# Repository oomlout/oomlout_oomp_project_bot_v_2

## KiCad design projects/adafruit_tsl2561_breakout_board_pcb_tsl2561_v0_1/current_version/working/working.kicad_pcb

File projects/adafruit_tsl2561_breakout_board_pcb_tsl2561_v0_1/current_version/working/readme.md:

# tsl2561_breakout_board_pcb
 
## summary 
* id: adafruit_tsl2561_breakout_board_pcb_tsl2561_v0_1
* user: adafruit
* name: tsl2561_breakout_board_pcb
* board: tsl2561_v0_1
* repo: https://github.com/adafruit/TSL2561-breakout-board-PCB

* src_file_repo_sch: 
* src_file_repo_sch_link: https://github.com/adafruit/TSL2561-breakout-board-PCB/tree/master/
* full details link: https://github.com/oomlout/oomlout_oomp_project_bot_v_2/tree/main/projects/adafruit_tsl2561_breakout_board_pcb_tsl2561_v0_1/current_version/working  

## schematic  
  
[schematic (pdf)](working_schematic.pdf) 

## pcb  

[board (pdf)](working.pdf)  

## working_bom
| Id | Designator | Footprint | Quantity | Designation | Supplier and ref |  | None | 
| --- | --- | --- | --- | --- | --- | --- | --- | 
| 1 | @HOLE1,@HOLE0 |  | 2 |  |  |  | [''] | 
| 2 | FID1,FID2 | FIDUCIAL_1MM | 2 | FIDUCIAL_1MM |  |  | [''] | 
| 3 | VIN_PAD0,SDA_PAD0,SCL_PAD0,GND_PAD0 | SEWALLI | 4 | SEWTAP-ALLIGATOR |  |  | [''] | 
| 4 | U$4 | STEMMA_TSL2561_B_FRONT | 1 |  |  |  | [''] | 
| 5 | X1 | JSTPH4 | 1 | STEMMA_I2C_RASMT |  |  | [''] | 
| 6 | C2,C1 | 0805-NO | 2 | 10uF |  |  | [''] | 
| 7 | R1 | RESPACK_4X0603 | 1 | 10K |  |  | [''] | 
| 8 | U2 | SOT23-5 | 1 | MIC5225-3.3 |  |  | [''] | 
| 9 | Q3 | SOT363 | 1 | 2N7002D |  |  | [''] | 
| 10 | U3 | TSL2561_FN | 1 | TSL2561 |  |  | [''] | 
| 11 | U$8 | PCBFEAT-REV-040 | 1 |  |  |  | [''] | 
| 12 | U$7 | STEMMA_TSL2561_B_BACK | 1 |  |  |  | [''] | 
| 13 | SJ1 | SOLDERJUMPER_2WAY_OPEN_NOPASTE | 1 |  |  |  | [''] | 

## bom_schematic
| Ref | Qnty | Value | Cmp name | Footprint | Description | Vendor | DNP | 
| --- | --- | --- | --- | --- | --- | --- | --- | 
| C1, C2 | 2 | 10uF | CAP_CERAMIC0805-NOOUTLINE | working:0805-NO |  |  |  | 
| FID1, FID2 | 2 | FIDUCIAL_1MM | FIDUCIAL_1MM | working:FIDUCIAL_1MM |  |  |  | 
| GND_PAD0 | 1 | SEWTAP-ALLIGATOR | SEWTAP-ALLIGATOR | working:SEWALLI |  |  |  | 
| Q3 | 1 | 2N7002D | MOSFET-N_DUAL | working:SOT363 |  |  |  | 
| R1 | 1 | 10K | RESISTOR_4PACK | working:RESPACK_4X0603 |  |  |  | 
| SCL_PAD0 | 1 | SEWTAP-ALLIGATOR | SEWTAP-ALLIGATOR | working:SEWALLI |  |  |  | 
| SDA_PAD0 | 1 | SEWTAP-ALLIGATOR | SEWTAP-ALLIGATOR | working:SEWALLI |  |  |  | 
| SJ1 | 1 | SOLDERJUMPER_2WAY | SOLDERJUMPER_2WAY | working:SOLDERJUMPER_2WAY_OPEN_NOPASTE |  |  |  | 
| U2 | 1 | MIC5225-3.3 | VREG_SOT23-5 | working:SOT23-5 |  |  |  | 
| U3 | 1 | TSL2561 | LIGHT_TSL2561 | working:TSL2561_FN |  |  |  | 
| VIN_PAD0 | 1 | SEWTAP-ALLIGATOR | SEWTAP-ALLIGATOR | working:SEWALLI |  |  |  | 
| X1 | 1 | STEMMA_I2C_RASMT | STEMMA_I2C_RASMT | working:JSTPH4 |  |  |  |

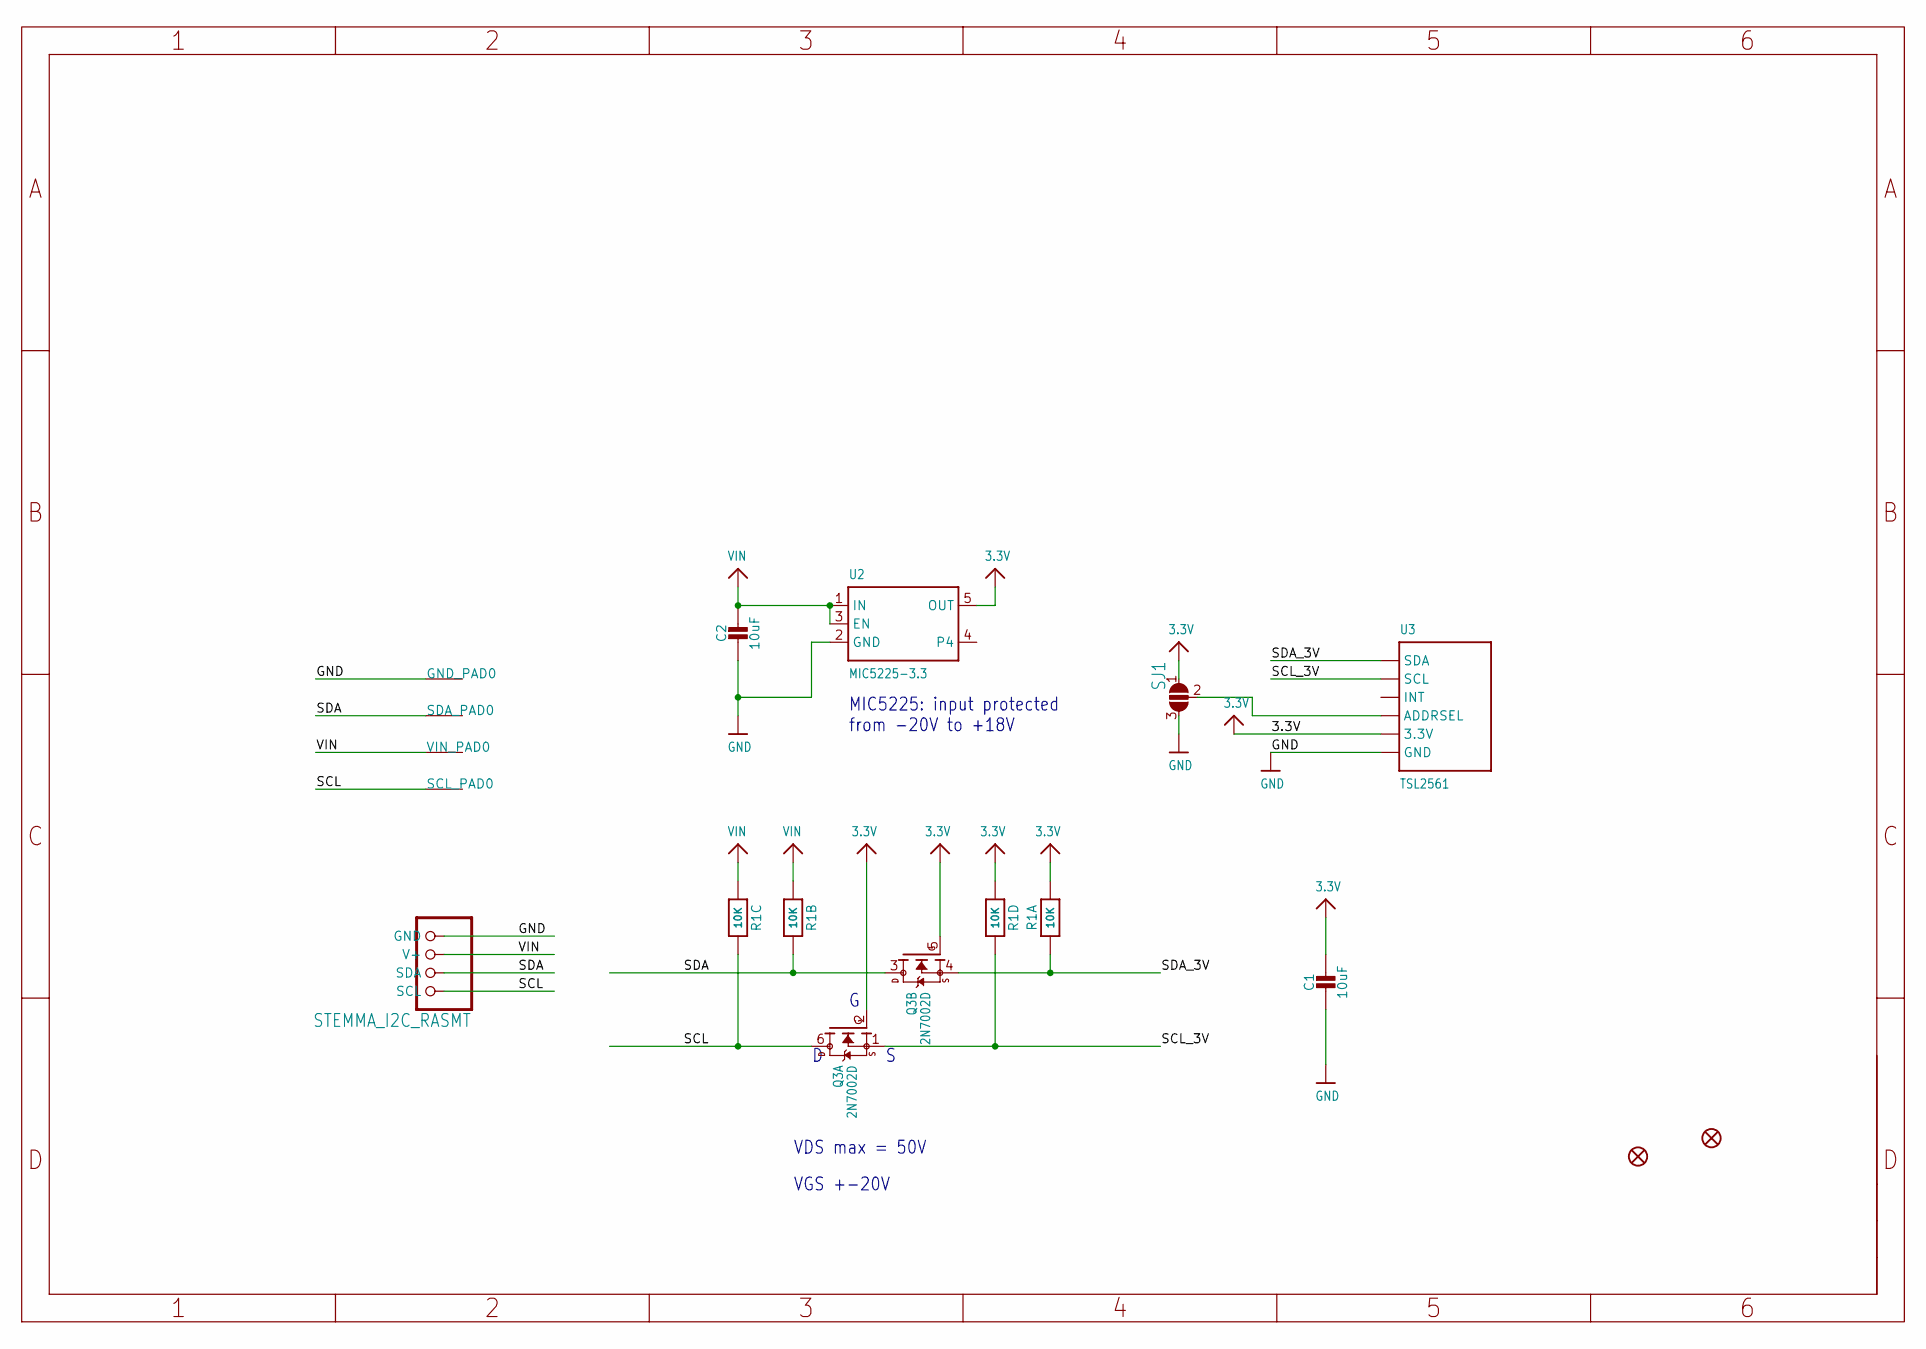
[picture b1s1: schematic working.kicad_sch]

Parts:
C1, C2: 10uF; 0805-NO
FID1, FID2: FIDUCIAL_1MM
GND_PAD0: SEWTAP-ALLIGATOR; SEWALLI
Q3: 2N7002D; SOT363
R1: 10K; RESPACK_4X0603
SCL_PAD0: SEWTAP-ALLIGATOR; SEWALLI
SDA_PAD0: SEWTAP-ALLIGATOR; SEWALLI
SJ1: SOLDERJUMPER_2WAY; SOLDERJUMPER_2WAY_OPEN_NOPASTE
U2: MIC5225-3.3; SOT23-5
U3: TSL2561; TSL2561_FN
VIN_PAD0: SEWTAP-ALLIGATOR; SEWALLI
X1: STEMMA_I2C_RASMT; JSTPH4

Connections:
3.3V: C1.1, Q3.2 (G), Q3.5 (G), R1.1, R1.5 (2), SJ1.1, U2.5 (OUT), U3.VDD (3.3V)
GND: C1.2, C2.2, GND_PAD0.P$1, SJ1.3, U2.2 (GND), U3.VSS (GND), X1.1 (GND)
unnamed: SJ1.2, U3.ADR (ADDRSEL)
SCL: Q3.6 (D), R1.6 (2), SCL_PAD0.P$1, X1.4 (SCL)
SCL_3V: Q3.1 (S), R1.4 (1), U3.CLK (SCL)
SDA: Q3.3 (D), R1.7 (2), SDA_PAD0.P$1, X1.3 (SDA)
SDA_3V: Q3.4 (S), R1.8 (2), U3.DATA (SDA)
VIN: C2.1, R1.2 (1), R1.3 (1), U2.1 (IN), U2.3 (EN), VIN_PAD0.P$1, X1.2 (V+)

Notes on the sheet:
VGS +-20V
MIC5225: input protected from -20V to +18V
VDS max = 50V

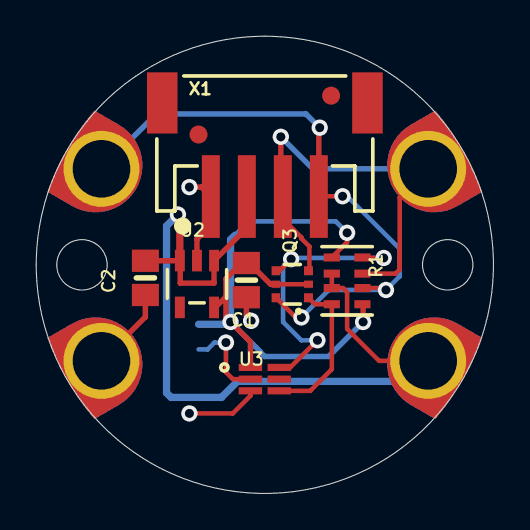
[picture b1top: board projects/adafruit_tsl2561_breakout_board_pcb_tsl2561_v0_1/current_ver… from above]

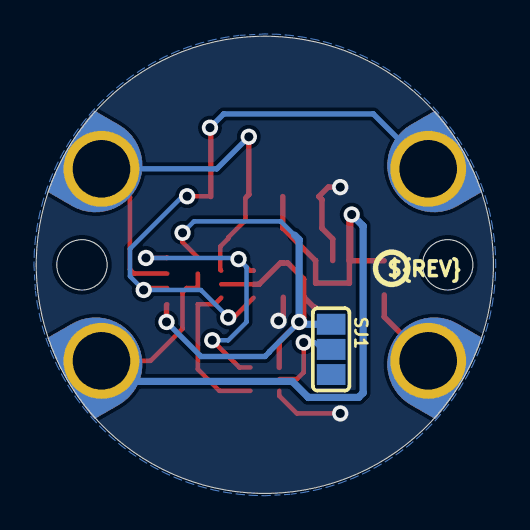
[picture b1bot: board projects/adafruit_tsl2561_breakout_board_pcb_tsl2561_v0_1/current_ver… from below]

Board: 2 copper layers, 25.4 x 25.4 mm, 19 parts (3 on the bottom side), 8 nets.

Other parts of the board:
@HOLE0, @HOLE1: (no value)
U$4: STEMMA_TSL2561_B_FRONT
U$7: STEMMA_TSL2561_B_BACK
U$8: PCBFEAT-REV-040

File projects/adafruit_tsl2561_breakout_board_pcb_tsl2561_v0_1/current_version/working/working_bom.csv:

"Id";"Designator";"Footprint";"Quantity";"Designation";"Supplier and ref";
1;"@HOLE1,@HOLE0";"";2;"";;;
2;"FID1,FID2";"FIDUCIAL_1MM";2;"FIDUCIAL_1MM";;;
3;"VIN_PAD0,SDA_PAD0,SCL_PAD0,GND_PAD0";"SEWALLI";4;"SEWTAP-ALLIGATOR";;;
4;"U$4";"STEMMA_TSL2561_B_FRONT";1;"";;;
5;"X1";"JSTPH4";1;"STEMMA_I2C_RASMT";;;
6;"C2,C1";"0805-NO";2;"10uF";;;
7;"R1";"RESPACK_4X0603";1;"10K";;;
8;"U2";"SOT23-5";1;"MIC5225-3.3";;;
9;"Q3";"SOT363";1;"2N7002D";;;
10;"U3";"TSL2561_FN";1;"TSL2561";;;
11;"U$8";"PCBFEAT-REV-040";1;"";;;
12;"U$7";"STEMMA_TSL2561_B_BACK";1;"";;;
13;"SJ1";"SOLDERJUMPER_2WAY_OPEN_NOPASTE";1;"";;;

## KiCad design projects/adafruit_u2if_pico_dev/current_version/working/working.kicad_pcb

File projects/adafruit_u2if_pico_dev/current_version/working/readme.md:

# u2if
 
## summary 
* id: adafruit_u2if_pico_dev
* user: adafruit
* name: u2if
* board: pico_dev
* repo: https://github.com/adafruit/u2if
* src_file_repo_kicad_pcb: board/pico-dev-v2/pico-dev.kicad_pcb
* src_file_repo_kicad_pcb_link: https://github.com/adafruit/u2if/tree/main/board/pico-dev-v2/pico-dev.kicad_pcb

* src_file_repo_sch: board/pico-dev-v2/pico-dev.sch
* src_file_repo_sch_link: https://github.com/adafruit/u2if/tree/main/board/pico-dev-v2/pico-dev.sch
* full details link: https://github.com/oomlout/oomlout_oomp_project_bot_v_2/tree/main/projects/adafruit_u2if_pico_dev/current_version/working  

## schematic  
  
[schematic (pdf)](working_schematic.pdf) 

## pcb  

[board (pdf)](working.pdf)  

## working_bom
| Id | Designator | Footprint | Quantity | Designation | Supplier and ref |  | None | 
| --- | --- | --- | --- | --- | --- | --- | --- | 
| 1 | U1 | RPi_Pico_SMD_TH | 1 | Pico |  |  | [''] | 
| 2 | U2 | ssd1306_I2c | 1 | SSD1306_I2C |  |  | [''] | 
| 3 | J10,J9 | PinHeader_1x06_P2.54mm_Vertical | 2 | SPI0 |  |  | [''] | 
| 4 | J8 | PinHeader_1x03_P2.54mm_Vertical | 1 | UART0 |  |  | [''] | 
| 5 | J17,J13 | PinHeader_1x03_P2.54mm_Vertical | 2 | +3.3V |  |  | [''] | 
| 6 | SW2 | SW_PUSH_6mm_H4.3mm | 1 | SW_GP9 |  |  | [''] | 
| 7 | SW3 | SW_PUSH_6mm_H4.3mm | 1 | SW_GP8 |  |  | [''] | 
| 8 | J3 | PinHeader_1x04_P2.54mm_Vertical | 1 | ANALOG |  |  | [''] | 
| 9 | J16,J15 | PinHeader_1x03_P2.54mm_Vertical | 2 | GND |  |  | [''] | 
| 10 | J19 | PinHeader_1x05_P2.54mm_Vertical | 1 | I2S |  |  | [''] | 
| 11 | C3,C4,C2,C5 | CP_Radial_D6.3mm_P2.50mm | 4 | CP |  |  | [''] | 
| 12 | SW1 | SW_PUSH_6mm_H4.3mm | 1 | RESET |  |  | [''] | 
| 13 | D2 | LED_1206_3216Metric_Pad1.42x1.75mm_HandSolder | 1 | LED |  |  | [''] | 
| 14 | R4 | R_1206_3216Metric_Pad1.42x1.75mm_HandSolder | 1 | 470 |  |  | [''] | 
| 15 | R3,R5,R2,R1,R6 | R_1206_3216Metric_Pad1.42x1.75mm_HandSolder | 5 | 10k |  |  | [''] | 
| 16 | J2 | PinHeader_1x04_P2.54mm_Vertical | 1 | SWD |  |  | [''] | 
| 17 | J21 | PinHeader_1x04_P2.54mm_Vertical | 1 | RGB |  |  | [''] | 
| 18 | JP1 | PinHeader_1x02_P2.54mm_Vertical | 1 | LCD_POWER |  |  | [''] | 
| 19 | J6,J5,J7 | PinHeader_1x04_P2.54mm_Vertical | 3 | I2C0 |  |  | [''] | 
| 20 | J20 | PinHeader_1x03_P2.54mm_Vertical | 1 | GPIO |  |  | [''] | 
| 21 | J18 | PinHeader_1x05_P2.54mm_Vertical | 1 | GPIO |  |  | [''] | 
| 22 | C1 | CP_Radial_D8.0mm_P3.50mm | 1 | CP |  |  | [''] | 
| 23 | J1 | PinHeader_1x02_P2.54mm_Vertical | 1 | MODE |  |  | [''] | 
| 24 | D1 | D_SMA | 1 | SS14 |  |  | [''] | 
| 25 | J22,J23 | PinHeader_1x04_P2.54mm_Vertical | 2 | I2C1 |  |  | [''] | 
| 26 | J14 | PinHeader_1x03_P2.54mm_Vertical | 1 | +5V |  |  | [''] | 
| 27 | J12 | PinHeader_1x06_P2.54mm_Vertical | 1 | SPI1/GPIO |  |  | [''] | 
| 28 | Q1 | SOT-23_Handsoldering | 1 | BSS138 |  |  | [''] | 

## bom_schematic
| Ref | Qnty | Value | Cmp name | Footprint | Description | Vendor | DNP | 
| --- | --- | --- | --- | --- | --- | --- | --- | 
| C1 | 1 | CP | CP-Device | Capacitor_THT:CP_Radial_D8.0mm_P3.50mm |  |  |  | 
| C2, C3, C4, C5 | 4 | CP | CP-Device | Capacitor_THT:CP_Radial_D6.3mm_P2.50mm |  |  |  | 
| D1 | 1 | SS14 | D_Schottky | Diode_SMD:D_SMA | Schottky diode |  |  | 
| D2 | 1 | LED | LED | LED_SMD:LED_1206_3216Metric_Pad1.42x1.75mm_HandSolder | Light emitting diode |  |  | 
| H1, H2, H3, H4 | 4 | MountingHole | MountingHole | MountingHole:MountingHole_3.2mm_M3 | Mounting Hole without connection |  |  | 
| J1 | 1 | MODE | Conn_01x02_Male-Connector | Connector_PinHeader_2.54mm:PinHeader_1x02_P2.54mm_Vertical |  |  |  | 
| J2 | 1 | SWD | Conn_01x04_Male-Connector | Connector_PinHeader_2.54mm:PinHeader_1x04_P2.54mm_Vertical |  |  |  | 
| J3 | 1 | ANALOG | Conn_01x04_Male-Connector | Connector_PinHeader_2.54mm:PinHeader_1x04_P2.54mm_Vertical |  |  |  | 
| J5, J6, J7 | 3 | I2C0 | Conn_01x04_Male-Connector | Connector_PinHeader_2.54mm:PinHeader_1x04_P2.54mm_Vertical |  |  |  | 
| J8 | 1 | UART0 | Conn_01x03_Male-Connector | Connector_PinHeader_2.54mm:PinHeader_1x03_P2.54mm_Vertical |  |  |  | 
| J9, J10 | 2 | SPI0 | Conn_01x06_Female-Connector | Connector_PinHeader_2.54mm:PinHeader_1x06_P2.54mm_Vertical |  |  |  | 
| J12 | 1 | SPI1/GPIO | Conn_01x06_Female-Connector | Connector_PinHeader_2.54mm:PinHeader_1x06_P2.54mm_Vertical |  |  |  | 
| J13, J17 | 2 | +3.3V | Conn_01x03_Male-Connector | Connector_PinHeader_2.54mm:PinHeader_1x03_P2.54mm_Vertical |  |  |  | 
| J14 | 1 | +5V | Conn_01x03_Male-Connector | Connector_PinHeader_2.54mm:PinHeader_1x03_P2.54mm_Vertical |  |  |  | 
| J15, J16 | 2 | GND | Conn_01x03_Male-Connector | Connector_PinHeader_2.54mm:PinHeader_1x03_P2.54mm_Vertical |  |  |  | 
| J18 | 1 | GPIO | Conn_01x05_Male-Connector | Connector_PinHeader_2.54mm:PinHeader_1x05_P2.54mm_Vertical |  |  |  | 
| J19 | 1 | I2S | Conn_01x05_Male-Connector | Connector_PinHeader_2.54mm:PinHeader_1x05_P2.54mm_Vertical |  |  |  | 
| J20 | 1 | GPIO | Conn_01x03_Male-Connector | Connector_PinHeader_2.54mm:PinHeader_1x03_P2.54mm_Vertical |  |  |  | 
| J21 | 1 | RGB | Conn_01x04_Male-Connector | Connector_PinHeader_2.54mm:PinHeader_1x04_P2.54mm_Vertical |  |  |  | 
| J22, J23 | 2 | I2C1 | Conn_01x04_Male-Connector | Connector_PinHeader_2.54mm:PinHeader_1x04_P2.54mm_Vertical |  |  |  | 
| JP1 | 1 | LCD_POWER | Jumper-Device | Connector_PinHeader_2.54mm:PinHeader_1x02_P2.54mm_Vertical |  |  |  | 
| Q1 | 1 | BSS138 | BSS138 | Package_TO_SOT_SMD:SOT-23_Handsoldering | 50V Vds, 0.22A Id, N-Channel MOSFET, SOT-23 |  |  | 
| R1, R2, R3, R5, R6 | 5 | 10k | R | Resistor_SMD:R_1206_3216Metric_Pad1.42x1.75mm_HandSolder | Resistor |  |  | 
| R4 | 1 | 470 | R | Resistor_SMD:R_1206_3216Metric_Pad1.42x1.75mm_HandSolder | Resistor |  |  | 
| SW1 | 1 | RESET | SW_Push | Button_Switch_THT:SW_PUSH_6mm_H4.3mm | Push button switch, generic, two pins |  |  | 
| SW2 | 1 | SW_GP9 | SW_Push | Button_Switch_THT:SW_PUSH_6mm_H4.3mm | Push button switch, generic, two pins |  |  | 
| SW3 | 1 | SW_GP8 | SW_Push | Button_Switch_THT:SW_PUSH_6mm_H4.3mm | Push button switch, generic, two pins |  |  | 
| U1 | 1 | Pico | Pico | MCU_RaspberryPi_and_Boards:RPi_Pico_SMD_TH |  |  |  | 
| U2 | 1 | SSD1306_I2C | SSD1306_I2C | oled_ssd1306:ssd1306_I2c | LCD 16x2 Alphanumeric gray backlight, 3 or 5 V VDD |  |  |

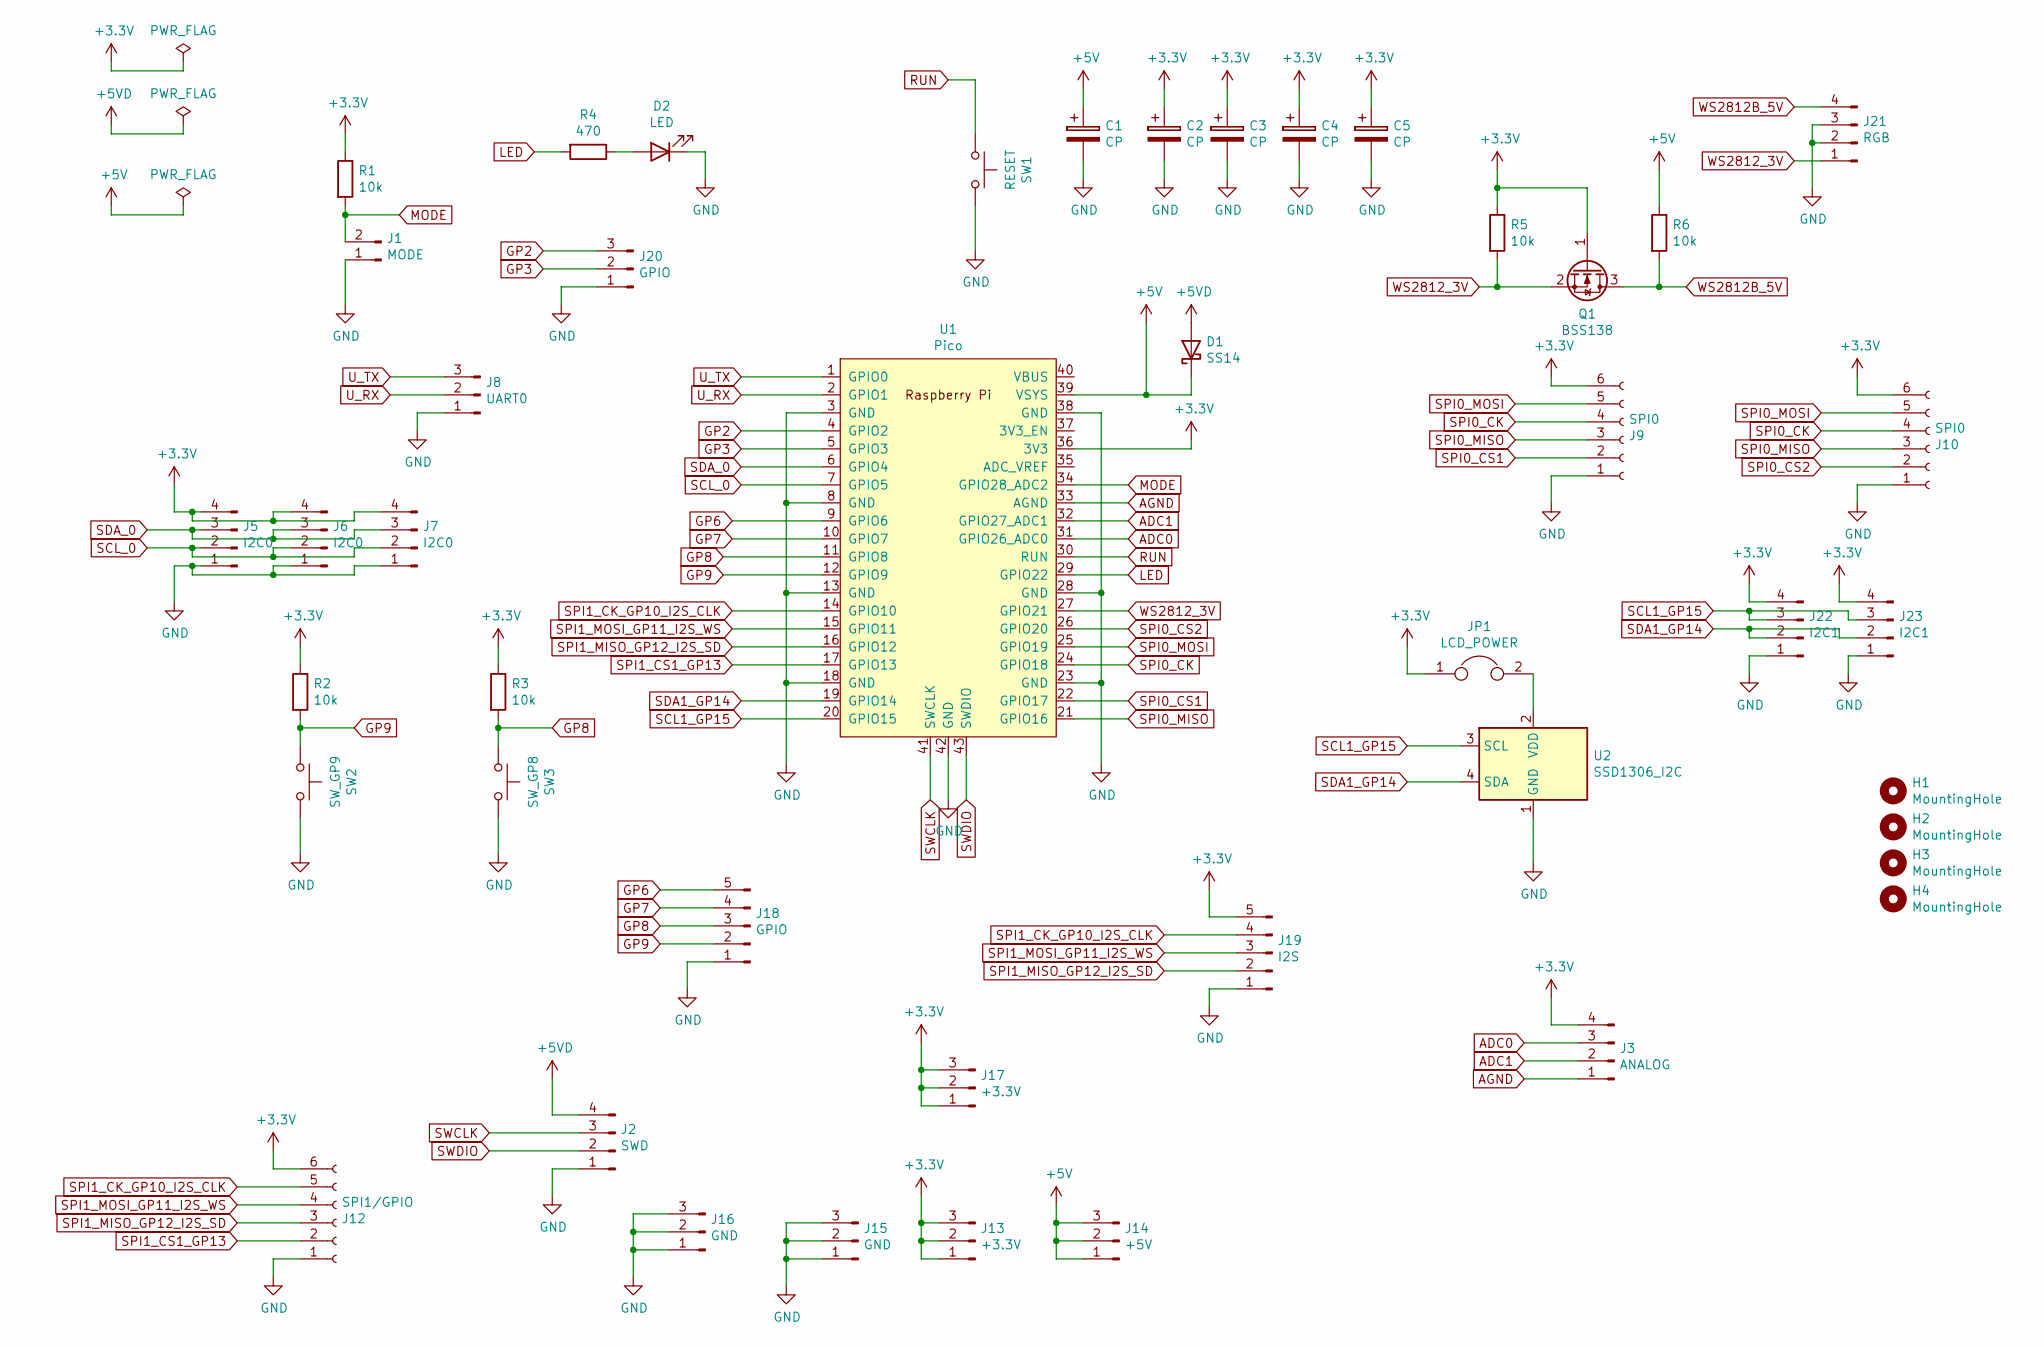
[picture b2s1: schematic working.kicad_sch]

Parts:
C1: CP; CP_Radial_D8.0mm_P3.50mm
C2, C3, C4, C5: CP; CP_Radial_D6.3mm_P2.50mm
D1: SS14; D_SMA
D2: LED; LED_1206_3216Metric_Pad1.42x1.75mm_HandSolder
H1, H2, H3, H4: MountingHole; MountingHole_3.2mm_M3
J1: MODE; PinHeader_1x02_P2.54mm_Vertical
J2: SWD; PinHeader_1x04_P2.54mm_Vertical
J3: ANALOG; PinHeader_1x04_P2.54mm_Vertical
J5, J6, J7: I2C0; PinHeader_1x04_P2.54mm_Vertical
J8: UART0; PinHeader_1x03_P2.54mm_Vertical
J9, J10: SPI0; PinHeader_1x06_P2.54mm_Vertical
J12: SPI1/GPIO; PinHeader_1x06_P2.54mm_Vertical
J13, J17: +3.3V; PinHeader_1x03_P2.54mm_Vertical
J14: +5V; PinHeader_1x03_P2.54mm_Vertical
J15, J16: GND; PinHeader_1x03_P2.54mm_Vertical
J18: GPIO; PinHeader_1x05_P2.54mm_Vertical
J19: I2S; PinHeader_1x05_P2.54mm_Vertical
J20: GPIO; PinHeader_1x03_P2.54mm_Vertical
J21: RGB; PinHeader_1x04_P2.54mm_Vertical
J22, J23: I2C1; PinHeader_1x04_P2.54mm_Vertical
JP1: LCD_POWER; PinHeader_1x02_P2.54mm_Vertical
Q1: BSS138; SOT-23_Handsoldering
R1, R2, R3, R5, R6: 10k; R_1206_3216Metric_Pad1.42x1.75mm_HandSolder
R4: 470; R_1206_3216Metric_Pad1.42x1.75mm_HandSolder
SW1: RESET; SW_PUSH_6mm_H4.3mm
SW2: SW_GP9; SW_PUSH_6mm_H4.3mm
SW3: SW_GP8; SW_PUSH_6mm_H4.3mm
U1: Pico; RPi_Pico_SMD_TH
U2: SSD1306_I2C; ssd1306_I2c

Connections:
+3V3: C2.1, C3.1, C4.1, C5.1, J3.4, J5.4, J6.4, J7.4, J9.6, J10.6, J12.6, J13.1, J13.2, J13.3, J17.1, J17.2, J17.3, J19.5, J22.4, J23.4, JP1.1, Q1.1 (G), R1.1, R2.1, R3.1, R5.1, U1.36 (3V3)
+5V: C1.1, D1.1 (K), J14.1, J14.2, J14.3, R6.1, U1.39 (VSYS)
+5VD: D1.2 (A), J2.4
ADC0: J3.3, U1.31 (GPIO26_ADC0)
ADC1: J3.2, U1.32 (GPIO27_ADC1)
AGND: J3.1, U1.33 (AGND)
GND: C1.2, C2.2, C3.2, C4.2, C5.2, D2.1 (K), J1.1, J2.1, J5.1, J6.1, J7.1, J8.1, J9.1, J10.1, J12.1, J15.1, J15.2, J15.3, J16.1, J16.2, J16.3, J18.1, J19.1, J20.1, J21.2, J21.3, J22.1, J23.1, SW1.2, SW2.2, SW3.2, U1.3 (GND), U1.8 (GND), U1.13 (GND), U1.18 (GND), U1.23 (GND), U1.28 (GND), U1.38 (GND), U1.42 (GND), U2.1 (GND)
GP2: J20.3, U1.4 (GPIO2)
GP3: J20.2, U1.5 (GPIO3)
GP6: J18.5, U1.9 (GPIO6)
GP7: J18.4, U1.10 (GPIO7)
GP8: J18.3, R3.2, SW3.1, U1.11 (GPIO8)
GP9: J18.2, R2.2, SW2.1, U1.12 (GPIO9)
LED: R4.2, U1.29 (GPIO22)
MODE: J1.2, R1.2, U1.34 (GPIO28_ADC2)
unnamed: D2.2 (A), R4.1
unnamed: JP1.2, U2.2 (VDD)
RUN: SW1.1, U1.30 (RUN)
SCL1_GP15: J22.3, J23.3, U1.20 (GPIO15), U2.3 (SCL)
SCL_0: J5.2, J6.2, J7.2, U1.7 (GPIO5)
SDA1_GP14: J22.2, J23.2, U1.19 (GPIO14), U2.4 (SDA)
SDA_0: J5.3, J6.3, J7.3, U1.6 (GPIO4)
SPI0_CK: J9.4, J10.4, U1.24 (GPIO18)
SPI0_CS1: J9.2, U1.22 (GPIO17)
SPI0_CS2: J10.2, U1.26 (GPIO20)
SPI0_MISO: J9.3, J10.3, U1.21 (GPIO16)
SPI0_MOSI: J9.5, J10.5, U1.25 (GPIO19)
SPI1_CK_GP10_I2S_CLK: J12.5, J19.4, U1.14 (GPIO10)
SPI1_CS1_GP13: J12.2, U1.17 (GPIO13)
SPI1_MISO_GP12_I2S_SD: J12.3, J19.2, U1.16 (GPIO12)
SPI1_MOSI_GP11_I2S_WS: J12.4, J19.3, U1.15 (GPIO11)
SWCLK: J2.3, U1.41 (SWCLK)
SWDIO: J2.2, U1.43 (SWDIO)
U_RX: J8.2, U1.2 (GPIO1)
U_TX: J8.3, U1.1 (GPIO0)
WS2812B_5V: J21.4, Q1.3 (D), R6.2
WS2812_3V: J21.1, Q1.2 (S), R5.2, U1.27 (GPIO21)

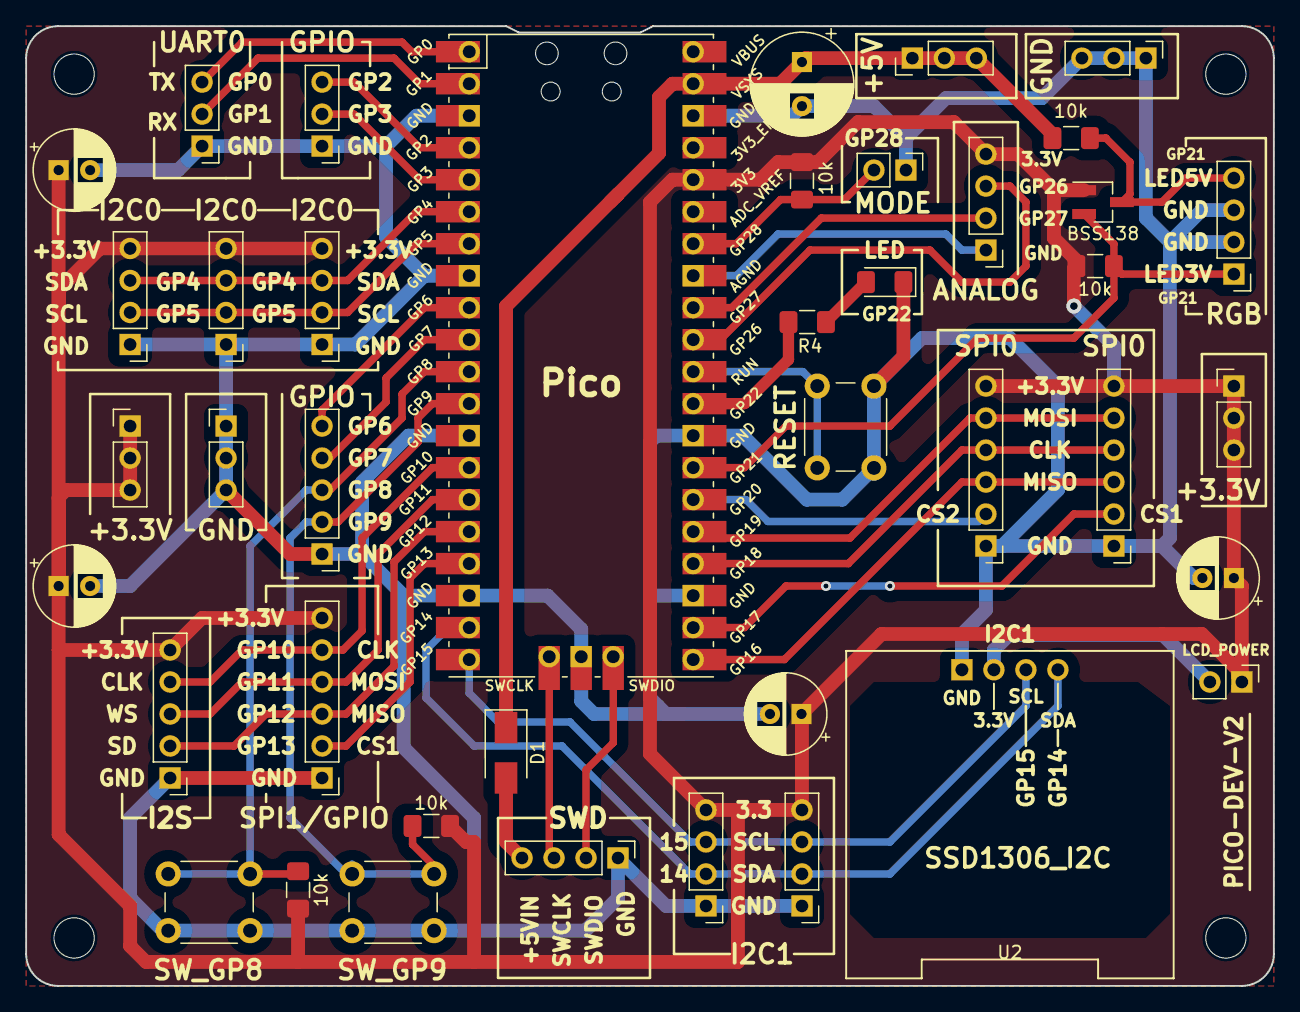
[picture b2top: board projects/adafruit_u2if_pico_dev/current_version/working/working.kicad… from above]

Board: 2 copper layers, 99.1 x 76.2 mm, 45 parts (0 on the bottom side), 37 nets.

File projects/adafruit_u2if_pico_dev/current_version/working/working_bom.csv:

"Id";"Designator";"Footprint";"Quantity";"Designation";"Supplier and ref";
1;"U1";"RPi_Pico_SMD_TH";1;"Pico";;;
2;"U2";"ssd1306_I2c";1;"SSD1306_I2C";;;
3;"J10,J9";"PinHeader_1x06_P2.54mm_Vertical";2;"SPI0";;;
4;"J8";"PinHeader_1x03_P2.54mm_Vertical";1;"UART0";;;
5;"J17,J13";"PinHeader_1x03_P2.54mm_Vertical";2;"+3.3V";;;
6;"SW2";"SW_PUSH_6mm_H4.3mm";1;"SW_GP9";;;
7;"SW3";"SW_PUSH_6mm_H4.3mm";1;"SW_GP8";;;
8;"J3";"PinHeader_1x04_P2.54mm_Vertical";1;"ANALOG";;;
9;"J16,J15";"PinHeader_1x03_P2.54mm_Vertical";2;"GND";;;
10;"J19";"PinHeader_1x05_P2.54mm_Vertical";1;"I2S";;;
11;"C3,C4,C2,C5";"CP_Radial_D6.3mm_P2.50mm";4;"CP";;;
12;"SW1";"SW_PUSH_6mm_H4.3mm";1;"RESET";;;
13;"D2";"LED_1206_3216Metric_Pad1.42x1.75mm_HandSolder";1;"LED";;;
14;"R4";"R_1206_3216Metric_Pad1.42x1.75mm_HandSolder";1;"470";;;
15;"R3,R5,R2,R1,R6";"R_1206_3216Metric_Pad1.42x1.75mm_HandSolder";5;"10k";;;
16;"J2";"PinHeader_1x04_P2.54mm_Vertical";1;"SWD";;;
17;"J21";"PinHeader_1x04_P2.54mm_Vertical";1;"RGB";;;
18;"JP1";"PinHeader_1x02_P2.54mm_Vertical";1;"LCD_POWER";;;
19;"J6,J5,J7";"PinHeader_1x04_P2.54mm_Vertical";3;"I2C0";;;
20;"J20";"PinHeader_1x03_P2.54mm_Vertical";1;"GPIO";;;
21;"J18";"PinHeader_1x05_P2.54mm_Vertical";1;"GPIO";;;
22;"C1";"CP_Radial_D8.0mm_P3.50mm";1;"CP";;;
23;"J1";"PinHeader_1x02_P2.54mm_Vertical";1;"MODE";;;
24;"D1";"D_SMA";1;"SS14";;;
25;"J22,J23";"PinHeader_1x04_P2.54mm_Vertical";2;"I2C1";;;
26;"J14";"PinHeader_1x03_P2.54mm_Vertical";1;"+5V";;;
27;"J12";"PinHeader_1x06_P2.54mm_Vertical";1;"SPI1/GPIO";;;
28;"Q1";"SOT-23_Handsoldering";1;"BSS138";;;

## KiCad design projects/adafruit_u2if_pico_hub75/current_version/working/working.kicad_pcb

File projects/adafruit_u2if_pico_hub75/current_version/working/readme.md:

# u2if
 
## summary 
* id: adafruit_u2if_pico_hub75
* user: adafruit
* name: u2if
* board: pico_hub75
* repo: https://github.com/adafruit/u2if
* src_file_repo_kicad_pcb: board/pico-hub75/pico-hub75.kicad_pcb
* src_file_repo_kicad_pcb_link: https://github.com/adafruit/u2if/tree/main/board/pico-hub75/pico-hub75.kicad_pcb

* src_file_repo_sch: board/pico-hub75/pico-hub75.sch
* src_file_repo_sch_link: https://github.com/adafruit/u2if/tree/main/board/pico-hub75/pico-hub75.sch
* full details link: https://github.com/oomlout/oomlout_oomp_project_bot_v_2/tree/main/projects/adafruit_u2if_pico_hub75/current_version/working  

## schematic  
  
[schematic (pdf)](working_schematic.pdf) 

## pcb  

[board (pdf)](working.pdf)  

## working_bom
| Id | Designator | Footprint | Quantity | Designation | Supplier and ref |  | None | 
| --- | --- | --- | --- | --- | --- | --- | --- | 
| 1 | U1 | RPi_Pico_SMD_TH | 1 | Pico |  |  | [''] | 
| 2 | J6,J7,J8 | PinHeader_1x03_P2.54mm_Vertical | 3 | Conn_01x03_Male |  |  | [''] | 
| 3 | SW3,SW1,SW2 | SW_PUSH_6mm_H5mm | 3 | SW_Push |  |  | [''] | 
| 4 | J5,J2 | PinHeader_1x06_P2.54mm_Vertical | 2 | Conn_01x06_Male |  |  | [''] | 
| 5 | J10,J9 | PinHeader_1x04_P2.54mm_Vertical | 2 | Conn_01x04_Male |  |  | [''] | 
| 6 | D1 | D_SMA | 1 | D_Schottky |  |  | [''] | 
| 7 | C5,C6,C8,C7 | CP_Radial_D6.3mm_P2.50mm | 4 | CP |  |  | [''] | 
| 8 | JP1,JP2 | PinHeader_1x02_P2.54mm_Vertical | 2 | Jumper |  |  | [''] | 
| 9 | J3 | PinHeader_1x05_P2.54mm_Vertical | 1 | Conn_01x05_Male |  |  | [''] | 
| 10 | J1 | IDC-Header_2x08_P2.54mm_Vertical | 1 | Conn_02x08_Odd_Even |  |  | [''] | 
| 11 | D2 | LED_1206_3216Metric_Pad1.42x1.75mm_HandSolder | 1 | LED |  |  | [''] | 
| 12 | R1,R2 | R_1206_3216Metric_Pad1.42x1.75mm_HandSolder | 2 | 10k |  |  | [''] | 
| 13 | R3 | R_1206_3216Metric_Pad1.42x1.75mm_HandSolder | 1 | 470 |  |  | [''] | 
| 14 | J4 | PinHeader_1x04_P2.54mm_Vertical | 1 | Conn_01x05_Male |  |  | [''] | 
| 15 | +5V,+3V3,GND | PinHeader_1x02_P2.54mm_Vertical | 3 | Conn_01x02_Male |  |  | [''] | 

## bom_schematic
| Ref | Qnty | Value | Cmp name | Footprint | Description | Vendor | DNP | 
| --- | --- | --- | --- | --- | --- | --- | --- | 
| C5, C6, C7, C8 | 4 | CP | CP-Device | Capacitor_THT:CP_Radial_D6.3mm_P2.50mm |  |  |  | 
| D1 | 1 | D_Schottky | D_Schottky | Diode_SMD:D_SMA | Schottky diode |  |  | 
| D2 | 1 | LED | LED | LED_SMD:LED_1206_3216Metric_Pad1.42x1.75mm_HandSolder | Light emitting diode |  |  | 
| H1, H2, H3, H4 | 4 | MountingHole | MountingHole | MountingHole:MountingHole_3.2mm_M3 | Mounting Hole without connection |  |  | 
| J1 | 1 | Conn_02x08_Odd_Even | Conn_02x08_Odd_Even | Connector_IDC:IDC-Header_2x08_P2.54mm_Vertical | Generic connector, double row, 02x08, odd/even pin numbering scheme (row 1 odd numbers, row 2 even numbers), script generated (kicad-library-utils/schlib/autogen/connector/) |  |  | 
| J2, J5 | 2 | Conn_01x06_Male | Conn_01x06_Male-Connector | Connector_PinHeader_2.54mm:PinHeader_1x06_P2.54mm_Vertical |  |  |  | 
| J3 | 1 | Conn_01x05_Male | Conn_01x05_Male-Connector | Connector_PinHeader_2.54mm:PinHeader_1x05_P2.54mm_Vertical |  |  |  | 
| J4 | 1 | Conn_01x05_Male | Conn_01x04_Male-Connector | Connector_PinHeader_2.54mm:PinHeader_1x04_P2.54mm_Vertical |  |  |  | 
| J6, J7, J8 | 3 | Conn_01x03_Male | Conn_01x03_Male-Connector | Connector_PinHeader_2.54mm:PinHeader_1x03_P2.54mm_Vertical |  |  |  | 
| J9, J10 | 2 | Conn_01x04_Male | Conn_01x04_Male-Connector | Connector_PinHeader_2.54mm:PinHeader_1x04_P2.54mm_Vertical |  |  |  | 
| J11, J12, J13 | 3 | Conn_01x02_Male | Conn_01x02_Male-Connector | Connector_PinHeader_2.54mm:PinHeader_1x02_P2.54mm_Vertical |  |  |  | 
| JP1, JP2 | 2 | Jumper | Jumper-Device | Connector_PinHeader_2.54mm:PinHeader_1x02_P2.54mm_Vertical |  |  |  | 
| R1, R2 | 2 | 10k | R | Resistor_SMD:R_1206_3216Metric_Pad1.42x1.75mm_HandSolder | Resistor |  |  | 
| R3 | 1 | 470 | R | Resistor_SMD:R_1206_3216Metric_Pad1.42x1.75mm_HandSolder | Resistor |  |  | 
| SW1, SW2, SW3 | 3 | SW_Push | SW_Push | Button_Switch_THT:SW_PUSH_6mm_H5mm | Push button switch, generic, two pins |  |  | 
| U1 | 1 | Pico | Pico | MCU_RaspberryPi_and_Boards:RPi_Pico_SMD_TH |  |  |  |

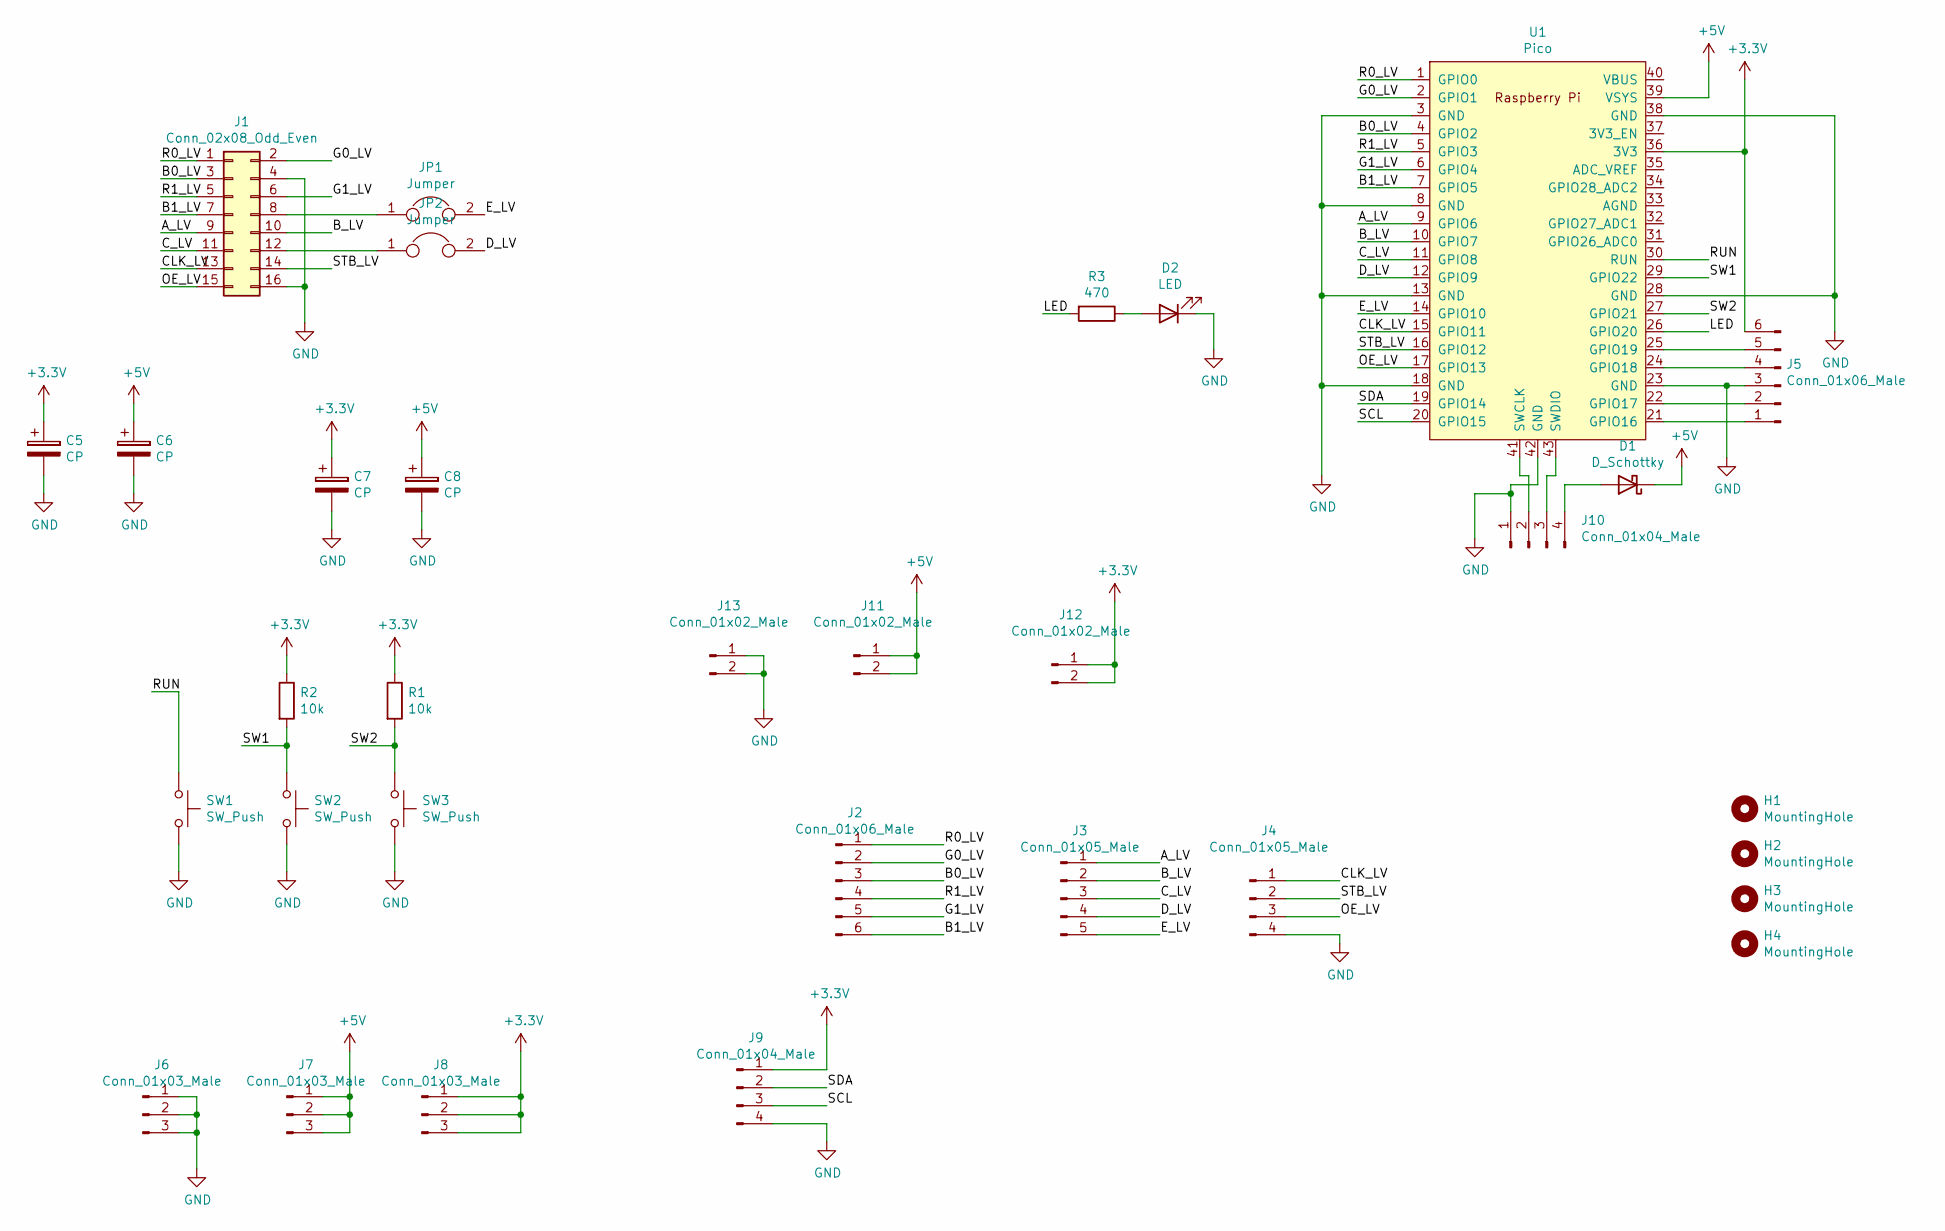
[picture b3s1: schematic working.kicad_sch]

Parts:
C5, C6, C7, C8: CP; CP_Radial_D6.3mm_P2.50mm
D1: D_Schottky; D_SMA
D2: LED; LED_1206_3216Metric_Pad1.42x1.75mm_HandSolder; LCSC C2296
H1, H2, H3, H4: MountingHole; MountingHole_3.2mm_M3
J1: Conn_02x08_Odd_Even; IDC-Header_2x08_P2.54mm_Vertical
J2, J5: Conn_01x06_Male; PinHeader_1x06_P2.54mm_Vertical
J3: Conn_01x05_Male; PinHeader_1x05_P2.54mm_Vertical
J4: Conn_01x05_Male; PinHeader_1x04_P2.54mm_Vertical
J6, J7, J8: Conn_01x03_Male; PinHeader_1x03_P2.54mm_Vertical
J9, J10: Conn_01x04_Male; PinHeader_1x04_P2.54mm_Vertical
J11, J12, J13: Conn_01x02_Male; PinHeader_1x02_P2.54mm_Vertical
JP1, JP2: Jumper; PinHeader_1x02_P2.54mm_Vertical
R1, R2: 10k; R_1206_3216Metric_Pad1.42x1.75mm_HandSolder; LCSC C17414
R3: 470; R_1206_3216Metric_Pad1.42x1.75mm_HandSolder; LCSC C17710
SW1, SW2, SW3: SW_Push; SW_PUSH_6mm_H5mm
U1: Pico; RPi_Pico_SMD_TH

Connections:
+3V3: C5.1, C7.1, J5.6, J8.1, J8.2, J8.3, J9.1, J12.1, J12.2, R1.1, R2.1, U1.36 (3V3); also elsewhere on the board
+5V: C6.1, C8.1, D1.1 (K), J7.1, J7.2, J7.3, J11.1, J11.2, U1.39 (VSYS); also elsewhere on the board
/A_LV: J1.9, J3.1, U1.9 (GPIO6)
/B0_LV: J1.3, J2.3, U1.4 (GPIO2)
/B1_LV: J1.7, J2.6, U1.7 (GPIO5)
/B_LV: J1.10, J3.2, U1.10 (GPIO7)
/CLK_LV: J1.13, J4.1, U1.15 (GPIO11)
/C_LV: J1.11, J3.3, U1.11 (GPIO8)
/D_LV: J3.4, JP2.2, U1.12 (GPIO9)
/E_LV: J3.5, JP1.2, U1.14 (GPIO10)
/G0_LV: J1.2, J2.2, U1.2 (GPIO1)
/G1_LV: J1.6, J2.5, U1.6 (GPIO4)
/LED: R3.2, U1.26 (GPIO20)
/OE_LV: J1.15, J4.3, U1.17 (GPIO13)
/R0_LV: J1.1, J2.1, U1.1 (GPIO0)
/R1_LV: J1.5, J2.4, U1.5 (GPIO3)
/RUN: SW1.1, U1.30 (RUN)
/SCL: J9.3, U1.20 (GPIO15)
/SDA: J9.2, U1.19 (GPIO14)
/STB_LV: J1.14, J4.2, U1.16 (GPIO12)
/SW1: R2.2, SW2.1, U1.29 (GPIO22)
/SW2: R1.2, SW3.1, U1.27 (GPIO21)
GND: C5.2, C6.2, C7.2, C8.2, D2.1 (K), J1.4, J1.16, J4.4, J5.3, J6.1, J6.2, J6.3, J9.4, J10.1, J13.1, J13.2, SW1.2, SW2.2, SW3.2, U1.3 (GND), U1.8 (GND), U1.13 (GND), U1.18 (GND), U1.23 (GND), U1.28 (GND), U1.38 (GND), U1.42 (GND); also elsewhere on the board
unnamed: D1.2 (A), J10.4
unnamed: D2.2 (A), R3.1
unnamed: J1.8, JP1.1
unnamed: J1.12, JP2.1
unnamed: J5.1, U1.21 (GPIO16)
unnamed: J5.2, U1.22 (GPIO17)
unnamed: J5.4, U1.24 (GPIO18)
unnamed: J5.5, U1.25 (GPIO19)
unnamed: J10.2, U1.41 (SWCLK)
unnamed: J10.3, U1.43 (SWDIO)

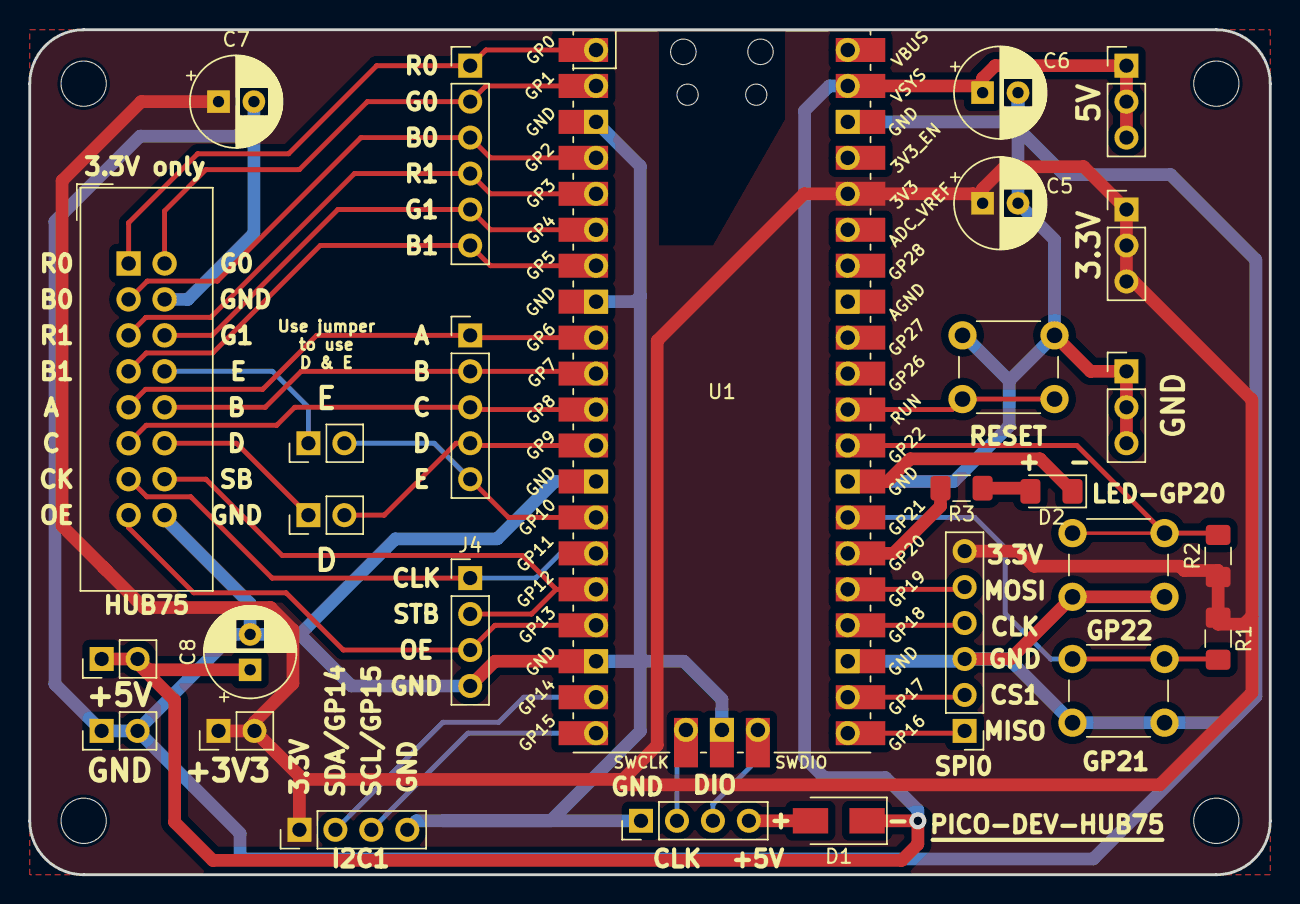
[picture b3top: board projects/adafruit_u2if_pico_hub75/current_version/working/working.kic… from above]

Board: 2 copper layers, 87.6 x 59.7 mm, 32 parts (0 on the bottom side), 33 nets.

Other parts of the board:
+3V3, +5V: Conn_01x02_Male; PinHeader_1x02_P2.54mm_Vertical
GND: Conn_01x02_Male; PinHeader_1x02_P2.54mm_Vertical

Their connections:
+3V3: +3V3.1, +3V3.2; also elsewhere on the board
+5V: +5V.1, +5V.2; also elsewhere on the board
GND: GND.1, GND.2; also elsewhere on the board

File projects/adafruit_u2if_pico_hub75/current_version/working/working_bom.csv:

"Id";"Designator";"Footprint";"Quantity";"Designation";"Supplier and ref";
1;"U1";"RPi_Pico_SMD_TH";1;"Pico";;;
2;"J6,J7,J8";"PinHeader_1x03_P2.54mm_Vertical";3;"Conn_01x03_Male";;;
3;"SW3,SW1,SW2";"SW_PUSH_6mm_H5mm";3;"SW_Push";;;
4;"J5,J2";"PinHeader_1x06_P2.54mm_Vertical";2;"Conn_01x06_Male";;;
5;"J10,J9";"PinHeader_1x04_P2.54mm_Vertical";2;"Conn_01x04_Male";;;
6;"D1";"D_SMA";1;"D_Schottky";;;
7;"C5,C6,C8,C7";"CP_Radial_D6.3mm_P2.50mm";4;"CP";;;
8;"JP1,JP2";"PinHeader_1x02_P2.54mm_Vertical";2;"Jumper";;;
9;"J3";"PinHeader_1x05_P2.54mm_Vertical";1;"Conn_01x05_Male";;;
10;"J1";"IDC-Header_2x08_P2.54mm_Vertical";1;"Conn_02x08_Odd_Even";;;
11;"D2";"LED_1206_3216Metric_Pad1.42x1.75mm_HandSolder";1;"LED";;;
12;"R1,R2";"R_1206_3216Metric_Pad1.42x1.75mm_HandSolder";2;"10k";;;
13;"R3";"R_1206_3216Metric_Pad1.42x1.75mm_HandSolder";1;"470";;;
14;"J4";"PinHeader_1x04_P2.54mm_Vertical";1;"Conn_01x05_Male";;;
15;"+5V,+3V3,GND";"PinHeader_1x02_P2.54mm_Vertical";3;"Conn_01x02_Male";;;

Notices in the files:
projects/adamgreig_amp_amp/current_version/working/working.kicad_sch:
Licence: CC-BY-SA
